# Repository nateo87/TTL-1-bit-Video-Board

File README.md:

# TTL-1-bit-Video-Board
<s><i><b>UPDATE 2/2/2025:</b></i>

Did another revision of the board. The one I had up here previously was one of my first projects in KiCad, moving away from EasyEDA. The main changes with this revision have to do with size: the board is MUCH smaller, and the footprints for a lot of the passive components have been assigned more appropriately sized designs. I also swapped out the no-longer-produced 74LS76 IC with the much easier to source 74LS109. Still functions the exact same, only difference is pinout and 'K' is now active LOW instead of HIGH. ANYWAYS, on to what I wrote previously: </s>

<b>UPDATE: 5/12/2025 </b>
Just built one of the newest revision, and whaddya know, a 74LS109 <i>will not</i> work in place of a 74LS76! I built a board over the weekend, and thought maybe I was dealing with bad PCB design that was creating ringing or cross-talk between signals. But nope - it has to use a <i>negative edge</i> triggered JK flip-flop instead of a positive edge trigger. I bodged in a 74LS112 and all was well. I'm currently working on a revision to use the 74LS112 instead. 

<b>UPDATE: 5/16/2025 </b>
I updated the board to use a (still produced) 74LS112 in place of the non-working 74LS109. Circuit should be fully functional now. Now to design a 3D printed enclosure!

<i>end of update</i>

Here is a TTL-based, 1-bit video board as designed by David L. Heiserman in the book How to Design and Build Your Own Custom TV Games. Corrections have been made from the schematics in the book, mostly just pin number confusions (the later schematics have much more troublesome errors).

The original design has the outputs all going to a card edge connector, but I thought a 40-pin IDC connector would be a little more friendly, and an adapter can easily be purchased so that an IDC cable can plug into a breadboard for experimentation. Another thing that has been changed from the original design is the analog video output. Though it is still B&W composite, the values of the resistors dividing the voltage have changed, in order to massage the signal to be more easily accepted among a wider range of RF modulators and monitors. Some TVs/monitors tend to be a little pickier about the signal being put into them. In my experimentation, most CRT TVs with a direct composite input tend to be more forgiving with the signal. Jumpers can be placed to activate an amplification of the video signal for more selective monitors.

The text of Heiserman's book can easily be found online on [archive.org](https://archive.org/details/howtodesignbuild0000heis_n7e2), and I highly encourage trying some of the builds in the book, if only so that I'm not the only one crazy enough to be working through them! I haven't ordered boards yet from this most recent revision (V3), but once I do, I'll have pics of the assembled product running some experiments. 

Here's a video of an earlier revision of the board running a simple moveable square circuit:

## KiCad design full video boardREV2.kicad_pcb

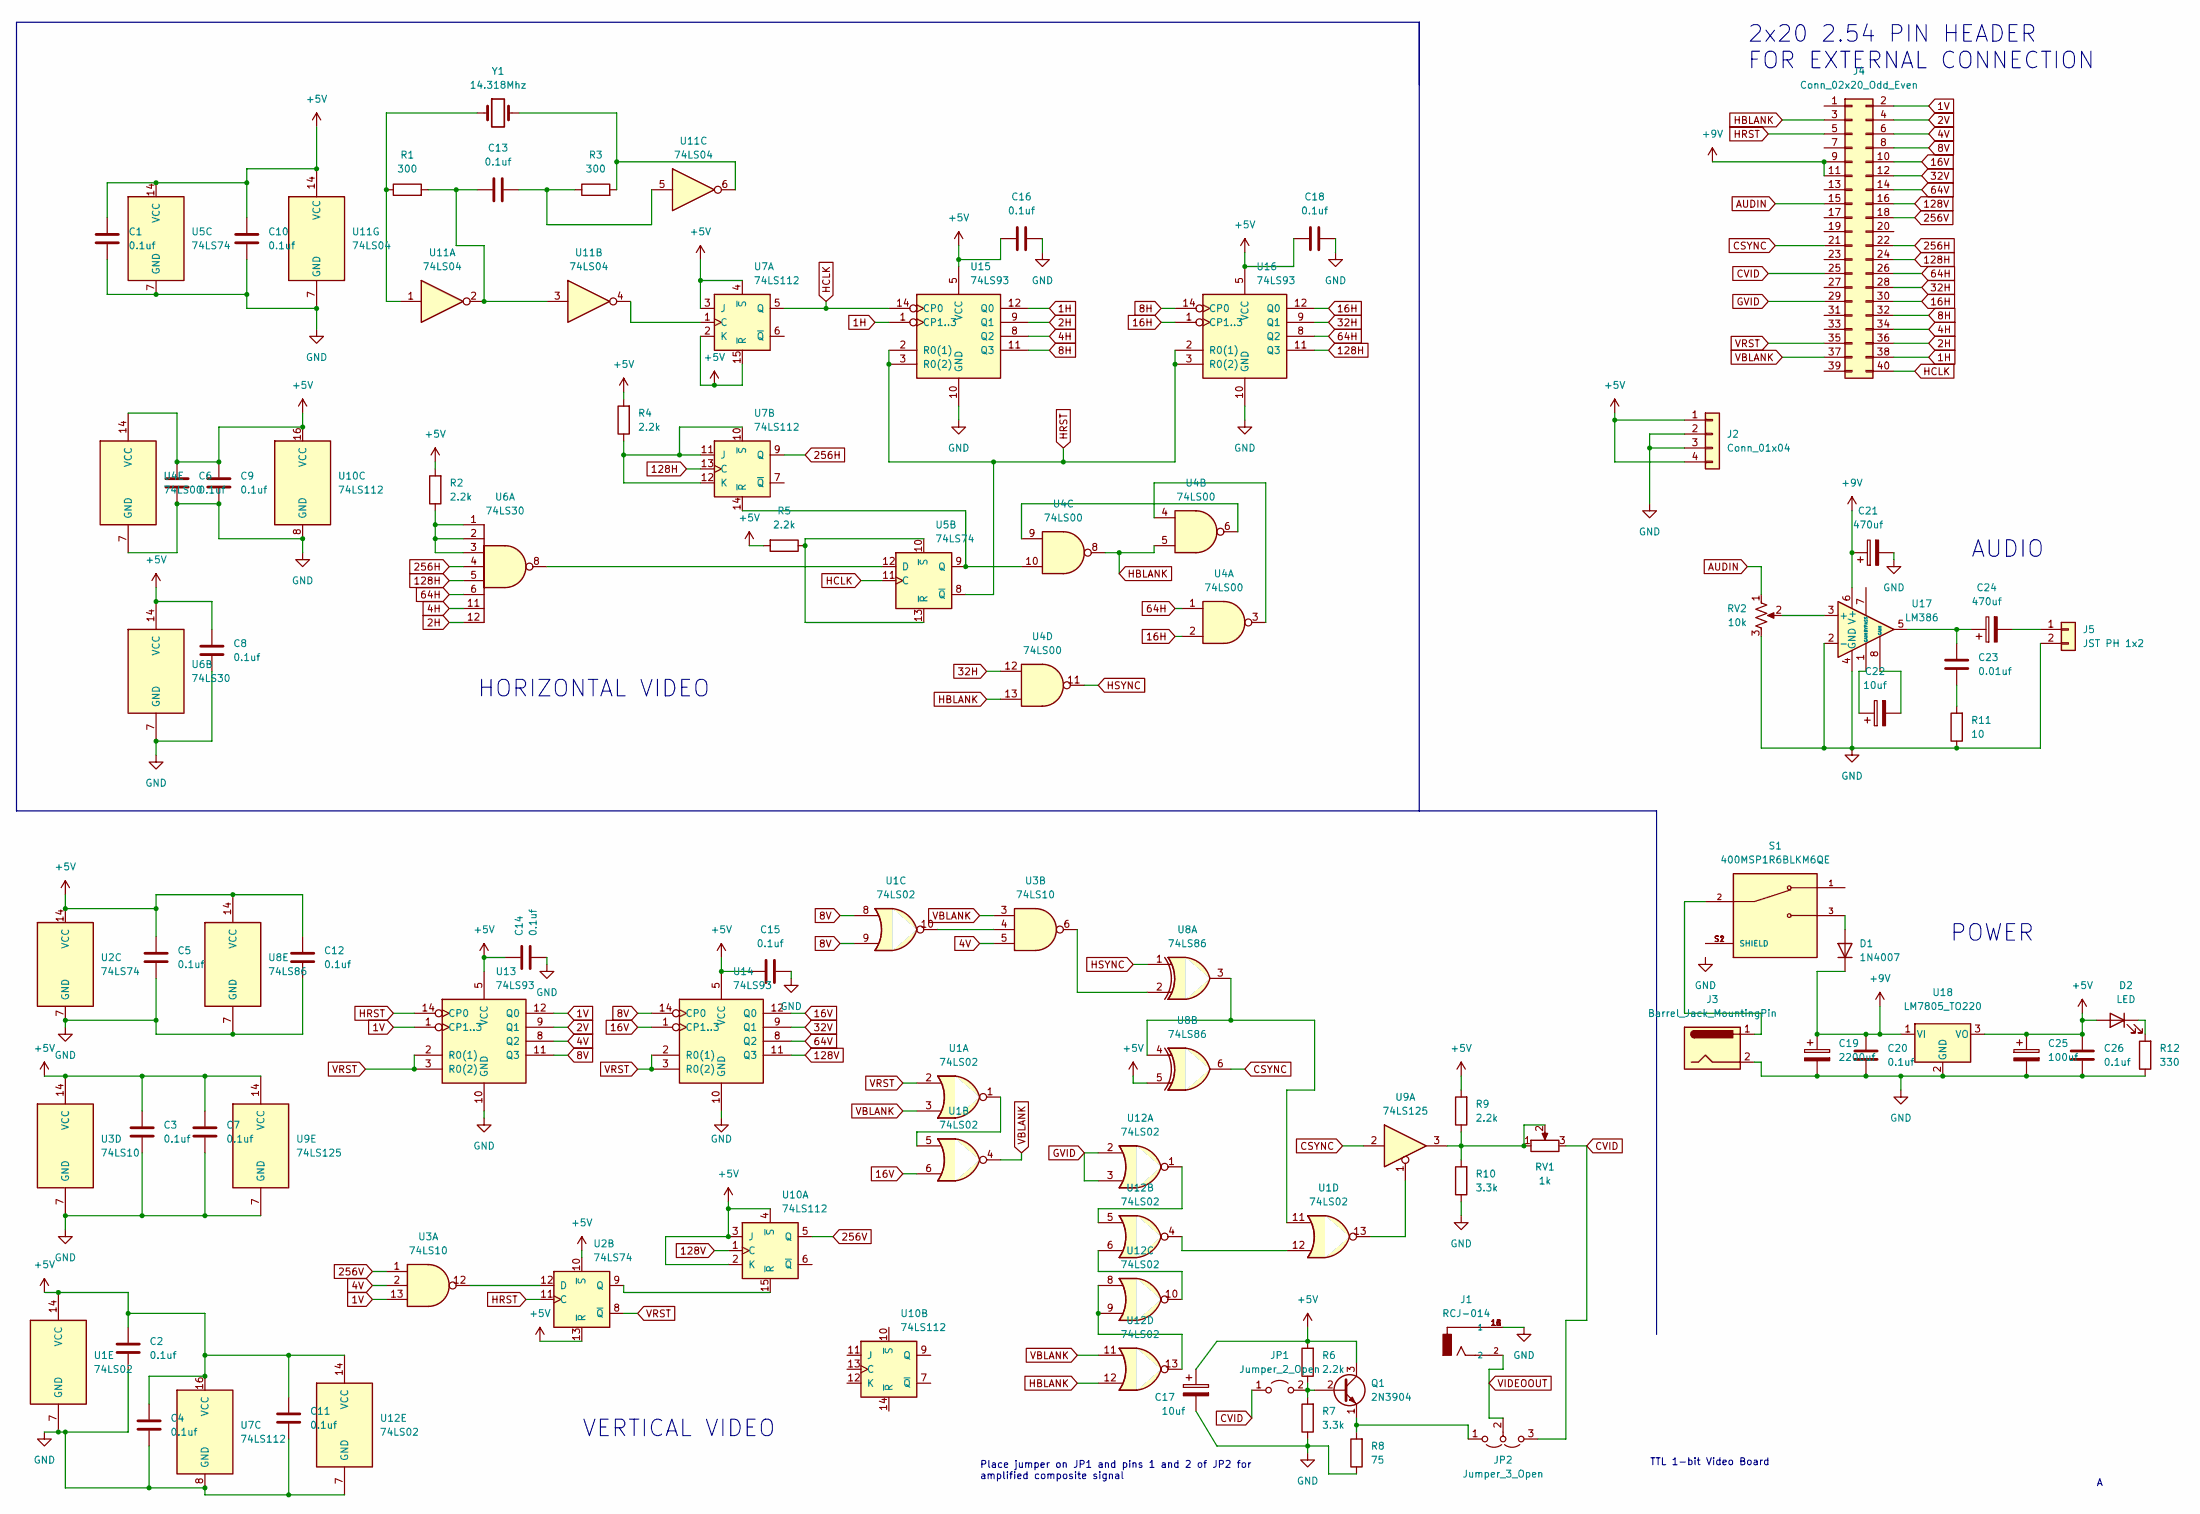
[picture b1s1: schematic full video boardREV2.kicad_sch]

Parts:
C1, C2, C3, C4, C5, C6, C7, C8, C9, C10, C11, C12, C14, C15, C16, C18: 0.1uf; C_Disc_D6.0mm_W2.5mm_P5.00mm
C13: 0.1uf; C_Rect_L4.0mm_W2.5mm_P2.50mm
C17, C22: 10uf; CP_Radial_D6.3mm_P2.50mm
C19: 2200uf; CP_Radial_D16.0mm_P7.50mm
C20, C26: 0.1uf; C_Disc_D6.0mm_W4.4mm_P5.00mm
C21, C24: 470uf; CP_Radial_D8.0mm_P3.80mm
C23: 0.01uf; C_Disc_D3.8mm_W2.6mm_P2.50mm
C25: 100uf; CP_Radial_D8.0mm_P3.50mm
D1: 1N4007; D_DO-41_SOD81_P10.16mm_Horizontal
D2: LED; LED_D5.0mm
J1: RCJ-014; CUI_RCJ-014; PART_REV B
J2: Conn_01x04; JST_VH_B4P-VH-B_1x04_P3.96mm_Vertical
J3: Barrel_Jack_MountingPin; BarrelJack_Horizontal
J4: Conn_02x20_Odd_Even; IDC-Header_2x20_P2.54mm_Vertical
J5: JST PH 1x2; JST_PH_B2B-PH-K_1x02_P2.00mm_Vertical
JP1: Jumper_2_Open; PinHeader_1x02_P2.54mm_Vertical
JP2: Jumper_3_Open; PinHeader_1x03_P2.54mm_Vertical
Q1: 2N3904; TO-92_Inline
R1, R3: 300; R_Axial_DIN0204_L3.6mm_D1.6mm_P7.62mm_Horizontal
R2, R4, R5, R6, R9: 2.2k; R_Axial_DIN0204_L3.6mm_D1.6mm_P7.62mm_Horizontal
R7, R10: 3.3k; R_Axial_DIN0204_L3.6mm_D1.6mm_P7.62mm_Horizontal
R8: 75; R_Axial_DIN0204_L3.6mm_D1.6mm_P7.62mm_Horizontal
R11: 10; R_Axial_DIN0309_L9.0mm_D3.2mm_P12.70mm_Horizontal
R12: 330; R_Axial_DIN0204_L3.6mm_D1.6mm_P7.62mm_Horizontal
RV1: 1k; Potentiometer_Bourns_3266Y_Vertical
RV2: 10k; Potentiometer_Piher_PT-6-V_Vertical_Hole
S1: 400MSP1R6BLKM6QE; SW_400MSP1R6BLKM6QE; PARTREV F
U1, U12: 74LS02; DIP-14_W7.62mm
U2, U5: 74LS74; DIP-14_W7.62mm
U3: 74LS10; DIP-14_W7.62mm
U4: 74LS00; DIP-14_W7.62mm
U6: 74LS30; DIP-14_W7.62mm
U7, U10: 74LS112
U8: 74LS86; DIP-14_W7.62mm
U9: 74LS125; DIP-14_W7.62mm
U11: 74LS04; DIP-14_W7.62mm
U13, U14, U15, U16: 74LS93; DIP-14_W7.62mm
U17: LM386; DIP-8_W7.62mm
U18: LM7805_TO220; TO-220-3_Vertical
Y1: 14.318Mhz; Crystal_HC18-U_Vertical

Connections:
1H: J4.38, U15.1 (CP1..3), U15.12 (Q0)
1V: J4.2, U3.13, U13.1 (CP1..3), U13.12 (Q0)
2H: J4.36, U6.12, U15.9 (Q1)
2V: J4.4, U13.9 (Q1)
4H: J4.34, U6.11, U15.8 (Q2)
4V: J4.6, U3.2, U3.5, U13.8 (Q2)
8H: J4.32, U15.11 (Q3), U16.14 (CP0)
8V: J4.8, U1.8, U1.9, U13.11 (Q3), U14.14 (CP0)
16H: J4.30, U4.2, U16.1 (CP1..3), U16.12 (Q0)
16V: J4.10, U1.6, U14.1 (CP1..3), U14.12 (Q0)
32H: J4.28, U4.12, U16.9 (Q1)
32V: J4.12, U14.9 (Q1)
64H: J4.26, U4.1, U6.6, U16.8 (Q2)
64V: J4.14, U14.8 (Q2)
128H: J4.24, U6.5, U7.13 (C), U16.11 (Q3)
128V: J4.16, U10.1 (C), U14.11 (Q3)
256H: J4.22, U6.4, U7.9 (Q)
256V: J4.18, U3.1, U10.5 (Q)
+5V: C1.1, C2.1, C3.1, C4.1, C5.1, C6.1, C7.1, C8.1, C9.1, C10.1, C11.1, C12.1, C14.1, C15.1, C16.1, C17.1, C18.1, C25.1, C26.1, D2.2 (A), J2.1, J2.4, Q1.3 (C), R2.2, R4.2, R5.2, R6.2, R9.2, U1.14 (VCC), U2.10 (~S), U2.13 (~R), U2.14 (VCC), U3.14 (VCC), U4.14 (VCC), U5.14 (VCC), U6.14 (VCC), U7.2 (K), U7.3 (J), U7.4 (~S), U7.15 (~R), U7.16 (VCC), U8.5, U8.14 (VCC), U9.14 (VCC), U10.2 (K), U10.3 (J), U10.4 (~S), U10.16 (VCC), U11.14 (VCC), U12.14 (VCC), U13.5 (VCC), U14.5 (VCC), U15.5 (VCC), U16.5 (VCC), U18.3 (VO)
+9V: C19.1, C20.1, C21.1, D1.1 (K), J4.9, J4.11, U17.6 (V+), U18.1 (VI)
AUDIN: J4.15, RV2.1
CSYNC: J4.21, U8.6, U9.2
CVID: J4.25, JP1.1 (A), JP2.3 (B), RV1.3
GVID: J4.29, U12.2, U12.3
HBLANK: J4.3, U4.5, U4.8, U4.13, U12.12
HCLK: J4.40, U5.11 (C), U7.5 (Q), U15.14 (CP0)
HRST: J4.5, U2.11 (C), U5.8 (~Q), U13.14 (CP0), U15.2 (R0(1)), U15.3 (R0(2)), U16.2 (R0(1)), U16.3 (R0(2))
HSYNC: U4.11, U8.1
unnamed: C13.1, R3.1, U11.5
unnamed: C13.2, R1.2, U11.2, U11.3
unnamed: C22.1, U17.1 (GAIN)
unnamed: C22.2, U17.8 (GAIN)
unnamed: C23.1, C24.1, U17.5
unnamed: C23.2, R11.2
unnamed: C24.2, J5.1
unnamed: D1.2 (A), S1.3
unnamed: D2.1 (K), R12.2
unnamed: J3.1, S1.2
unnamed: JP1.2 (B), Q1.2 (B), R6.1, R7.2
unnamed: JP2.1 (A), Q1.1 (E), R8.2
unnamed: R1.1, U11.1, Y1.1
unnamed: R2.1, U6.1, U6.2, U6.3
unnamed: R3.2, U11.6, Y1.2
unnamed: R4.1, U7.10 (~S), U7.11 (J), U7.12 (K)
unnamed: R5.1, U5.10 (~S), U5.13 (~R)
unnamed: R9.1, R10.2, RV1.1, RV1.2, U9.3
unnamed: RV2.2, U17.3 (+)
unnamed: U1.1, U1.5
unnamed: U1.10, U3.4
unnamed: U1.11, U8.3, U8.4
unnamed: U1.12, U12.4
unnamed: U1.13, U9.1
unnamed: U2.12 (D), U3.12
unnamed: U3.6, U8.2
unnamed: U4.3, U4.4
unnamed: U4.6, U4.9
unnamed: U4.10, U5.9 (Q), U7.14 (~R)
unnamed: U5.12 (D), U6.8
unnamed: U2.9 (Q), U10.15 (~R)
unnamed: U7.1 (C), U11.4
unnamed: U12.1, U12.5
unnamed: U12.6, U12.10
unnamed: U12.8, U12.9, U12.13
VBLANK: J4.37, U1.3, U1.4, U3.3, U12.11
VIDEOOUT: J1.2, JP2.2 (C)
VRST: J4.35, U1.2, U2.8 (~Q), U13.2 (R0(1)), U13.3 (R0(2)), U14.2 (R0(1)), U14.3 (R0(2))

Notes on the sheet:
Place jumper on JP1 and pins 1 and 2 of JP2 for amplified composite signal
TTL 1-bit Video Board
POWER
HORIZONTAL VIDEO
2x20 2.54 PIN HEADER FOR EXTERNAL CONNECTION
AUDIO
VERTICAL VIDEO

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
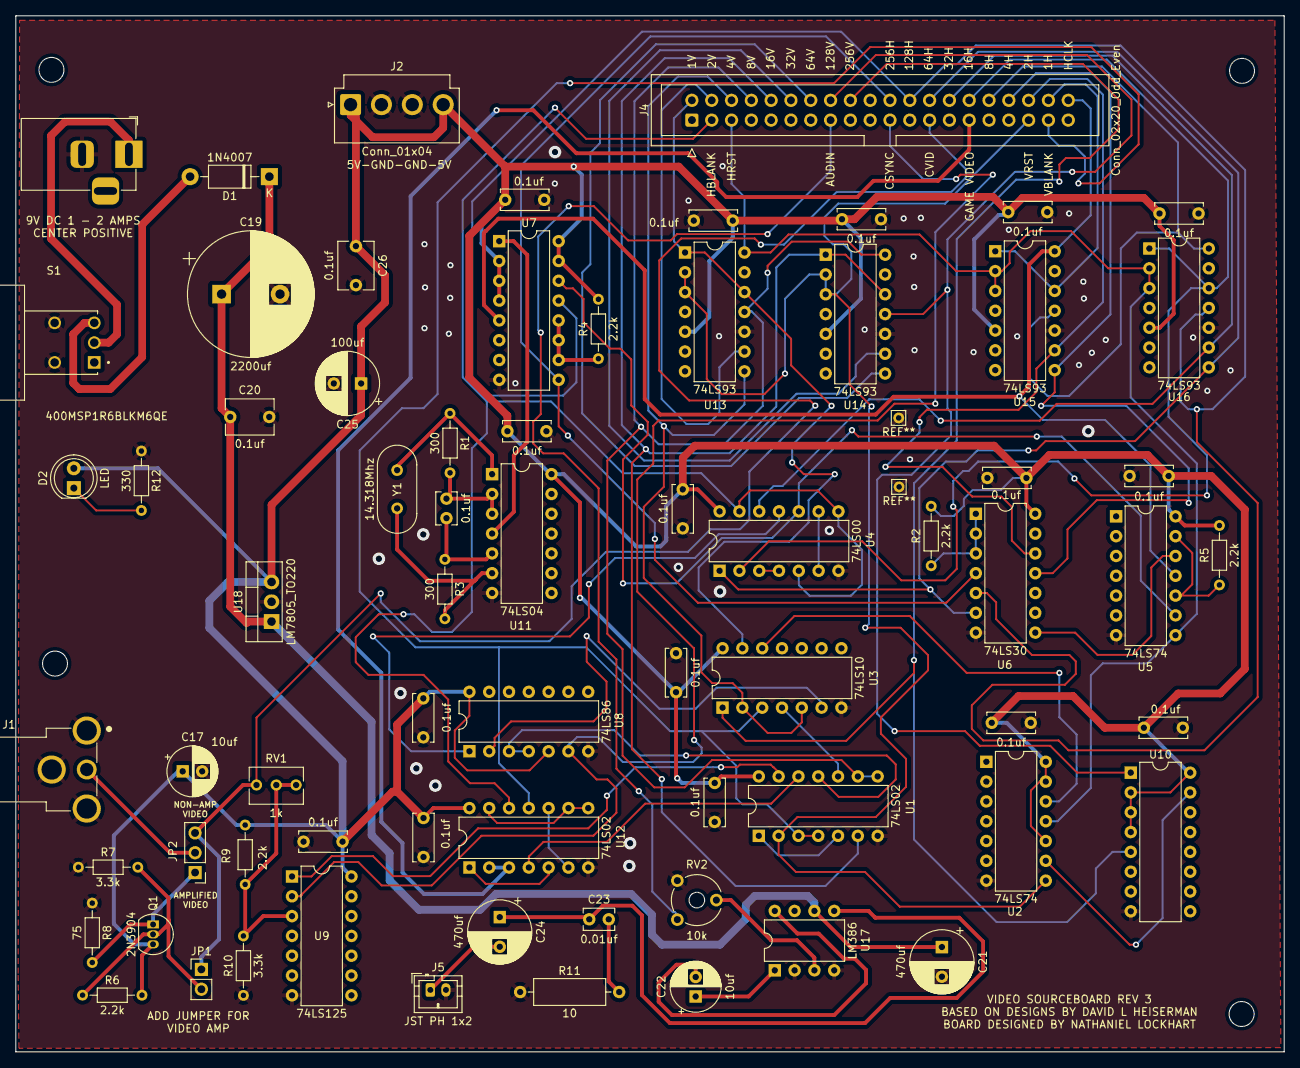
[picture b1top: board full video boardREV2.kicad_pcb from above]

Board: 2 copper layers, 162.6 x 132.8 mm, 70 parts (0 on the bottom side), 67 nets.

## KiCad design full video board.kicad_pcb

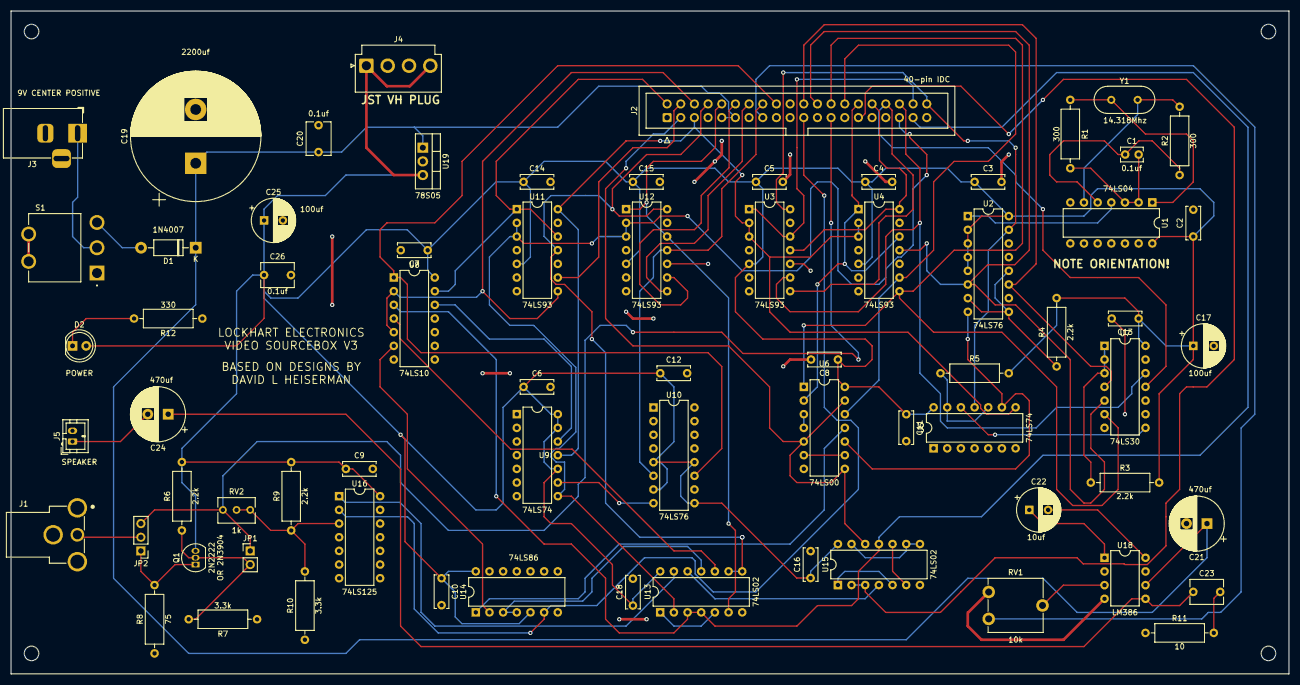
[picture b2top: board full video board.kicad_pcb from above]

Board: 2 copper layers, 237.5 x 123.2 mm, 70 parts (0 on the bottom side), 68 nets.

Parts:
C1: 0.1uf; C_Rect_L4.0mm_W2.5mm_P2.50mm
C2, C3, C4, C5, C6, C7, C8, C9, C10, C11, C12, C13, C14, C15, C16, C18: 0.1uf; C_Disc_D6.0mm_W2.5mm_P5.00mm
C17: 100uf; CP_Radial_D8.0mm_P3.80mm
C19: 2200uf; CP_Radial_D24.0mm_P10.00mm_SnapIn
C20, C26: 0.1uf; C_Disc_D6.0mm_W4.4mm_P5.00mm
C21, C24: 470uf; CP_Radial_D10.0mm_P3.80mm
C22: 10uf; CP_Radial_D8.0mm_P3.50mm
C23: 0.01uf; C_Disc_D6.0mm_W4.4mm_P5.00mm
C25: 100uf; CP_Radial_D8.0mm_P3.50mm
D1: 1N4007; D_DO-41_SOD81_P10.16mm_Horizontal
D2: LED; LED_D5.0mm
J1: RCJ-014; CUI_RCJ-014
J2: Conn_02x20_Odd_Even; IDC-Header_2x20_P2.54mm_Vertical
J3: Barrel_Jack_MountingPin; BarrelJack_Horizontal
J4: Conn_01x04; JST_VH_B4P-VH-B_1x04_P3.96mm_Vertical
J5: JST PH 1x2; JST_PH_B2B-PH-K_1x02_P2.00mm_Vertical
JP1: Jumper_2_Open; PinHeader_1x02_P2.54mm_Vertical
JP2: Jumper_3_Open; PinHeader_1x03_P2.54mm_Vertical
Q1: 2N3904; TO-92_Inline
R1, R2: 300; R_Axial_DIN0309_L9.0mm_D3.2mm_P12.70mm_Horizontal
R3, R4, R5, R6, R9: 2.2k; R_Axial_DIN0309_L9.0mm_D3.2mm_P12.70mm_Horizontal
R7, R10: 3.3k; R_Axial_DIN0309_L9.0mm_D3.2mm_P12.70mm_Horizontal
R8: 75; R_Axial_DIN0309_L9.0mm_D3.2mm_P12.70mm_Horizontal
R11: 10; R_Axial_DIN0309_L9.0mm_D3.2mm_P12.70mm_Horizontal
R12: 330; R_Axial_DIN0309_L9.0mm_D3.2mm_P12.70mm_Horizontal
RV1: 10k; Potentiometer_ACP_CA9-V10_Vertical
RV2: 1k; Potentiometer_Bourns_3266Y_Vertical
S1: 300SP1J1BLKM6QE; SW_300SP1J1BLKM6QE
U1: 74LS04; DIP-14_W7.62mm
U2, U10: 74LS76; DIP-16_W7.62mm
U3, U4, U11, U12: 74LS93; DIP-14_W7.62mm
U5, U9: 74LS74; DIP-14_W7.62mm
U6: 74LS00; DIP-14_W7.62mm
U7: 74LS30; DIP-14_W7.62mm
U8: 74LS10; DIP-14_W7.62mm
U13, U15: 74LS02; DIP-14_W7.62mm
U14: 74LS86; DIP-14_W7.62mm
U16: 74LS125; DIP-14_W7.62mm
U18: LM386; DIP-8_W7.62mm
U19: LM7805_TO220; TO-220-3_Vertical
Y1: 14.318Mhz; Crystal_HC18-U_Vertical

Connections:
1H: J2.38, U3.1 (CP1..3), U3.12 (Q0)
1V: J2.2, U8.13, U11.1 (CP1..3), U11.12 (Q0)
2H: J2.36, U3.9 (Q1), U7.12
2V: J2.4, U11.9 (Q1)
4H: J2.34, U3.8 (Q2), U7.11
4V: J2.6, U8.2, U8.5, U11.8 (Q2)
8H: J2.32, U3.11 (Q3), U4.14 (CP0)
8V: J2.8, U11.11 (Q3), U12.14 (CP0), U13.8, U13.9
16H: J2.30, U4.1 (CP1..3), U4.12 (Q0), U6.2
16V: J2.10, U12.1 (CP1..3), U12.12 (Q0), U13.6
32H: J2.28, U4.9 (Q1), U6.12
32V: J2.12, U12.9 (Q1)
64H: J2.26, U4.8 (Q2), U6.1, U7.6
64V: J2.14, U12.8 (Q2)
128H: J2.24, U2.6 (C), U4.11 (Q3), U7.5
128V: J2.16, U10.6 (C), U12.11 (Q3)
256H: J2.22, U2.11 (Q), U7.4
256V: J2.18, U8.1, U10.11 (Q)
+5V: C2.1, C3.1, C4.1, C5.1, C6.1, C7.1, C8.1, C9.1, C10.1, C11.1, C12.1, C13.1, C14.1, C15.1, C16.1, C17.1, C18.1, C25.1, C26.1, D2.2 (A), J4.1, J4.4, Q1.3 (C), R3.2, R4.2, R5.2, R6.2, R9.2, U1.14 (VCC), U2.2 (~S), U2.3 (~R), U2.4 (J), U2.5 (VCC), U2.16 (K), U3.5 (VCC), U4.5 (VCC), U5.14 (VCC), U6.14 (VCC), U7.14 (VCC), U8.14 (VCC), U9.10 (~S), U9.13 (~R), U9.14 (VCC), U10.5 (VCC), U10.7 (~S), U10.9 (J), U10.12 (K), U11.5 (VCC), U12.5 (VCC), U13.14 (VCC), U14.5, U14.14 (VCC), U15.14 (VCC), U16.14 (VCC), U19.3 (VO)
+9V: C19.1, C20.1, C21.1, D1.1 (K), J2.9, J2.11, U18.6 (V+), U19.1 (VI)
AUDIN: J2.15, RV1.1
CSYNC: J2.21, U14.6, U16.2
CVID: J2.25, JP1.1 (A), JP2.3 (B), RV2.3
GND: C2.2, C3.2, C4.2, C5.2, C6.2, C7.2, C8.2, C9.2, C10.2, C11.2, C12.2, C13.2, C14.2, C15.2, C16.2, C17.2, C18.2, C19.2, C20.2, C21.2, C25.2, C26.2, J1.1A (1), J1.1B (1), J1.1C (1), J3.2, J4.2, J4.3, J5.2, R7.1, R8.1, R10.1, R11.1, R12.1, RV1.3, U1.7 (GND), U2.13 (GND), U3.10 (GND), U4.10 (GND), U5.7 (GND), U6.7 (GND), U7.7 (GND), U8.7 (GND), U9.7 (GND), U10.13 (GND), U11.10 (GND), U12.10 (GND), U13.7 (GND), U14.7 (GND), U15.7 (GND), U16.7 (GND), U18.2 (-), U18.4 (GND), U19.2 (GND)
GVID: J2.29, U15.2, U15.3
HBLANK: J2.3, U6.5, U6.8, U6.13, U15.12
HCLK: J2.40, U2.15 (Q), U3.14 (CP0), U5.11 (C)
HRST: J2.5, U3.2 (R0(1)), U3.3 (R0(2)), U4.2 (R0(1)), U4.3 (R0(2)), U5.8 (~Q), U9.11 (C), U11.14 (CP0)
HSYNC: U6.11, U14.1
unnamed: C1.1, R2.1, U1.5
unnamed: C1.2, R1.2, U1.2, U1.3
unnamed: C22.1, U18.1 (GAIN)
unnamed: C22.2, U18.8 (GAIN)
unnamed: C23.1, C24.1, U18.5
unnamed: C23.2, R11.2
unnamed: C24.2, J5.1
unnamed: D1.2 (A), S1.3
unnamed: D2.1 (K), R12.2
unnamed: J3.1, S1.2
unnamed: JP2.1 (A), Q1.1 (E), R8.2
unnamed: JP1.2 (B), Q1.2 (B), R6.1, R7.2
unnamed: R1.1, U1.1, Y1.1
unnamed: R2.2, U1.6, Y1.2
unnamed: R3.1, U7.1, U7.2, U7.3
unnamed: R4.1, U2.7 (~S), U2.9 (J), U2.12 (K)
unnamed: R5.1, U5.10 (~S), U5.13 (~R)
unnamed: R9.1, R10.2, RV2.1, RV2.2, U16.3
unnamed: RV1.2, U18.3 (+)
unnamed: S1.S1 (SHIELD), S1.S2 (SHIELD)
unnamed: U1.4, U2.1 (C)
unnamed: U2.8 (~R), U5.9 (Q), U6.10
unnamed: U5.12 (D), U7.8
unnamed: U6.3, U6.4
unnamed: U6.6, U6.9
unnamed: U8.4, U13.10
unnamed: U8.12, U9.12 (D)
unnamed: U9.9 (Q), U10.8 (~R)
unnamed: U13.1, U13.5
unnamed: U13.11, U14.3, U14.4
unnamed: U13.12, U15.4
unnamed: U13.13, U16.1
unnamed: U8.6, U14.2
unnamed: U15.1, U15.5
unnamed: U15.6, U15.10
unnamed: U15.8, U15.9, U15.13
VBLANK: J2.37, U8.3, U13.3, U13.4, U15.11
VIDEOOUT: J1.2, JP2.2 (C)
VRST: J2.35, U9.8 (~Q), U11.2 (R0(1)), U11.3 (R0(2)), U12.2 (R0(1)), U12.3 (R0(2)), U13.2

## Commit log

2025-02-02 Update README.md
    Mentioning new board revision and changes contained therein.
2025-02-02 Create README.md
    explaining old files
2025-02-02 Rename full video board.pdf to OLD/full video board.pdf
2025-02-02 new gerbers for new pcb revision
2025-02-02 Rename full video boardREV3.zip to gerbers/full video boardREV3.zip
2025-05-12 Update README.md
    Putting in crucial updated info
2025-05-17 Delete gerbers directory
    old gerbers for previous revision with incorrect flip-flop IC; replacing with correct ones
2025-05-17 Add files via upload
    Updated KiCad project files.
